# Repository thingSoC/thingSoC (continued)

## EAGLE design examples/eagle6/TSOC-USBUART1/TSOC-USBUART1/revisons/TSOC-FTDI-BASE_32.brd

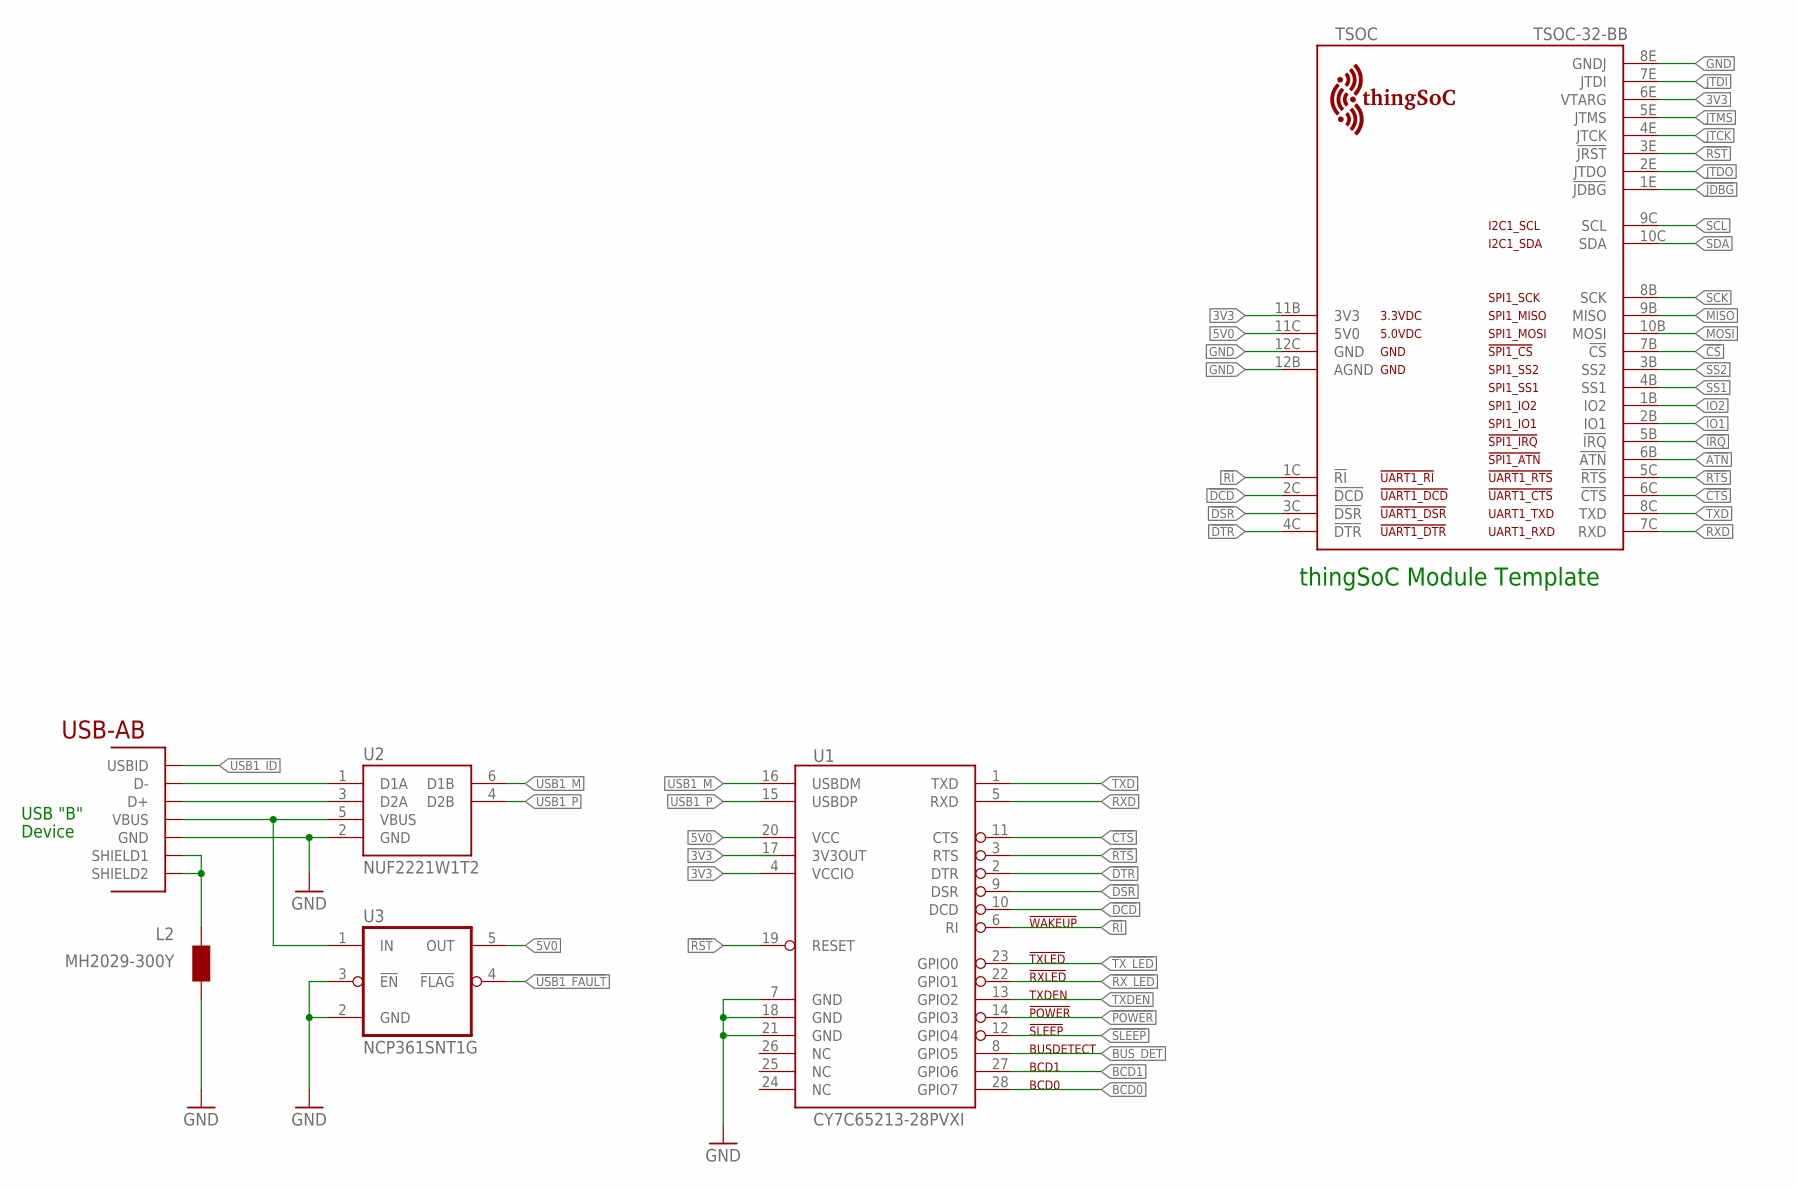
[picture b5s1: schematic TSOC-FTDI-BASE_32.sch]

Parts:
L2: MH2029-300Y; 0805
TSOC: TSOC-32-BB; TSOC-BB-S32
U1: CY7C65213-28PVXI; SSOP28DB
U2: NUF2221W1T2; SOT-363
U3: NCP361SNT1G; SOP95P275X110-5N
USB1: USB_AB; USB-AB-MICRO-SMD

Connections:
3V3: TSOC.6E (VTARG), TSOC.11B (3V3), U1.4 (VCCIO)
5V0: TSOC.11C (5V0), U1.20 (VCC), U3.5 (OUT)
!ATN: TSOC.6B (!ATN)
!CS: TSOC.7B (!CS)
!CTS: TSOC.6C (!CTS), U1.11 (CTS)
!DCD: TSOC.2C (!DCD), U1.10 (DCD)
!DSR: TSOC.3C (!DSR), U1.9 (DSR)
!DTR: TSOC.4C (!DTR), U1.2 (DTR)
!IRQ: TSOC.5B (!IRQ)
!JDBG: TSOC.1E (!JDBG)
!POWER: U1.14 (GPIO3)
!RI: TSOC.1C (!RI), U1.6 (RI)
!RST: TSOC.3E (!JRST), U1.19 (RESET)
!RTS: TSOC.5C (!RTS), U1.3 (RTS)
!RX_LED: U1.22 (GPIO1)
!SLEEP: U1.12 (GPIO4)
!TX_LED: U1.23 (GPIO0)
!USB1_FAULT: U3.4 (!FLAG)
BCD0: U1.28 (GPIO7)
BCD1: U1.27 (GPIO6)
BUS_DET: U1.8 (GPIO5)
GND: L2.2, TSOC.8E (GNDJ), TSOC.12B (AGND), TSOC.12C (GND), U1.7 (GND), U1.18 (GND), U1.21 (GND), U2.2 (GND), U3.2 (GND), U3.3 (!EN), USB1.GND
IO1: TSOC.2B (IO1)
IO2: TSOC.1B (IO2)
JTCK: TSOC.4E (JTCK)
JTDI: TSOC.7E (JTDI)
JTDO: TSOC.2E (JTDO)
JTMS: TSOC.5E (JTMS)
MISO: TSOC.9B (MISO)
MOSI: TSOC.10B (MOSI)
NC: U1.24 (NC), U1.25 (NC)
RXD: TSOC.7C (RXD), U1.5 (RXD)
SCK: TSOC.8B (SCK)
SCL: TSOC.9C (SCL)
SDA: TSOC.10C (SDA)
SS1: TSOC.4B (SS1)
SS2: TSOC.3B (SS2)
TXD: TSOC.8C (TXD), U1.1 (TXD)
TXDEN: U1.13 (GPIO2)
USB1_DM: U2.1 (D1A), USB1.D-
USB1_DP: U2.3 (D2A), USB1.D+
USB1_ID: USB1.ID (USBID)
USB1_M: U1.16 (USBDM), U2.6 (D1B)
USB1_P: U1.15 (USBDP), U2.4 (D2B)
USB1_SHIELD: L2.1, USB1.SHIELD1, USB1.SHIELD2
USB1_VBUS: U2.5 (VBUS), U3.1 (IN), USB1.VBUS

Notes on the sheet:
thingSoC Module Template
USB "B"
Device

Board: 2 copper layers, 6 parts (0 on the bottom side), 19 nets, no tracks yet.

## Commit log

2015-01-18 placeholder
2015-04-01 Update Logo
2015-04-02 alpha 0.8
2015-04-06 add 6 pin versions
2015-04-08 lbr update - add smd outlines
2015-04-10 update 0.86 - grid fixes
2015-04-10 update 0.87 - 90deg rotate
2015-04-14 update keying icon
2015-05-01 update thingSoC libraries
2015-05-02 correct 40 pin device outlines
2015-05-05 thingSoC Spec update
2015-11-13 24 Pin update
2015-11-22 add embbeded modules
2015-11-26 embedded module updates
2015-12-05 update modules
2015-12-07 add USBUART1 Reference Design
2015-12-08 add Encore3SoC thingSoC reference design
2015-12-08 add ignores
2015-12-08 rebuild
2015-12-08 add embedded modules
2015-12-18 add mux comments
2016-05-23 update borad outline
2016-06-18 update board outlines
2016-07-18 update thingsoc eagle templates centroids
2016-07-18 update eagle template centroids
2016-07-21 update eagle libraryt descriptions
2016-10-29 update PCB libs
